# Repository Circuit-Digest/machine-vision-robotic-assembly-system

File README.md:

<div align="center">

# 🤖 Machine Vision-Based Robotic Assembly System Using MechArm 270 and Jetson Nano

**A real-time computer-vision system that drives a 6-DOF robotic arm + linear rail to autonomously assemble two toy cars, verifying every part placement using black-pixel ROI detection on an on-board webcam.**

<br><br>

</div>

---

## 📖 Table of Contents

1. [Project Overview](#-project-overview)
2. [Key Features](#-key-features)
3. [System Architecture](#-system-architecture)
4. [Hardware Requirements](#-hardware-requirements)
5. [Software Requirements & Installation](#-software-requirements--installation)
6. [Configuration](#-configuration)
7. [Running the Server](#-running-the-server)
8. [Dashboard Guide](#-dashboard-guide)
9. [Calibration Workflow](#-calibration-workflow)
10. [Vision Pipeline](#-vision-pipeline)
11. [Inspection Stations](#-inspection-stations)
12. [Waypoint System](#-waypoint-system)
13. [Socket.IO Event Reference](#-socketio-event-reference)
14. [Project Structure](#-project-structure)
15. [Troubleshooting](#-troubleshooting)
16. [Contributing](#-contributing)
17. [License](#-license)

---

## 🎯 Project Overview

This system orchestrates a **MechArm 270** 6-DOF robotic arm mounted on a **stepper-driven linear rail** to perform automated, vision-verified pick-and-place assembly of two toy cars.

The arm visits five physical stations. At each inspection station it positions its **wrist-mounted webcam** over a part tray, and a real-time OpenCV pipeline **verifies the correct component is present** using black-pixel ROI analysis before the arm is allowed to pick it up. A missing part immediately halts the sequence, triggers a **physical buzzer alert**, and waits for an operator to place the correct component.

The entire stack — robot control, vision processing, rail control, and web dashboards — runs as a **single Python process on port 5000**, eliminating all inter-service network latency.

---

## ✨ Key Features

| Feature | Description |
|---|---|
| 🎥 **Live MJPEG Stream** | Real-time webcam feed with annotated ROI overlays served to the browser |
| 🔍 **Black-Pixel ROI Detection** | Station-aware part detection using calibrated bounding boxes and HSV black masking |
| 🤖 **Wi-Fi Arm Control** | Non-blocking TCP socket control of MechArm 270 via `pymycobot` |
| 🚂 **ESP32 Rail Control** | HTTP-driven stepper linear rail with 5 presets (P1–P5) |
| 🚦 **Physical Indicators** | Green/Red LED + buzzer relay control for workshop-audible alerts |
| ✅ **Assembly Checklist** | Live progress bar and per-part checklist updating on every verification |
| 🖥️ **Three Dashboards** | Home display, Operator dashboard, Waypoint editor — all browser-based |
| 🛡️ **Sim Mode Fallback** | Full simulation when no hardware is connected — no code changes needed |
| 💾 **JSON Persistence** | All waypoints, poses, ROIs, and network config survive server restarts |

---

## 🏗️ System Architecture

```
┌─────────────────────────────────────────────────────────────────┐
│            main.py  (single process, port 5000)       │
│                                                                  │
│  ┌──────────────┐   ┌──────────────┐   ┌─────────────────────┐ │
│  │ RobotManager │   │  RailManager │   │  RailIndicatorMgr   │ │
│  │  Wi-Fi TCP   │   │  HTTP / ESP32│   │  HTTP relay control  │ │
│  └──────┬───────┘   └──────┬───────┘   └──────────┬──────────┘ │
│         │                  │                        │            │
│  ┌──────▼──────────────────▼───────────────────────▼──────────┐ │
│  │                   PlaybackEngine                            │ │
│  │  Sequences arm + rail movements + vision verification       │ │
│  └──────────────────────────┬──────────────────────────────────┘ │
│                             │  shared in-process memory           │
│  ┌──────────────────────────▼──────────────────────────────────┐ │
│  │             vision_thread()  (~30 FPS)                      │ │
│  │   OpenCV: Black-pixel ROI detection per station             │ │
│  └─────────────────────────────────────────────────────────────┘ │
│                                                                  │
│  Flask Routes + Socket.IO  →  Browser Dashboards                │
└─────────────────────────────────────────────────────────────────┘
```

### Data Flow

```
Camera → vision_thread → stable_detected_parts (dict)
                              ↓ (zero-latency in-process read)
                         PlaybackEngine → verifies part → continues sequence
                              ↓
                         Socket.IO → Browser (checklist, log, progress)
```

---

## 🔧 Hardware Requirements

| Component | Specification | Notes |
|---|---|---|
| **Robot Arm** | Elephant Robotics MechArm 270 | Wi-Fi model required |
| **Linear Rail** | Custom stepper rail with ESP32-C6 | 5 presets: P1–P5 |
| **Camera** | USB webcam (640×480 minimum) | Wrist-mounted on arm |
| **Relay Board** | 3-channel relay (12V) | Buzzer + Green/Red LED |
| **Network** | Wi-Fi AP or router | Arm, ESP32, and host PC on same LAN |
| **Host Computer** | Any x86/ARM Linux or Windows PC | Python 3.9+ required |

> [!NOTE]
> The system runs in full **simulation mode** if no hardware is connected. The camera stream is replaced by an animated mock feed, all Socket.IO events fire normally, and you can test the complete UI and checklist flow without any physical hardware.

---

## 💻 Software Requirements & Installation

### 1. Clone the repository

```bash
git clone https://github.com/YOUR_USERNAME/machine-vision-robotic-assembly-system.git
cd machine-vision-robotic-assembly-system
```

### 2. Create a virtual environment (recommended)

```bash
python -m venv venv

# Windows
venv\Scripts\activate

# Linux / macOS
source venv/bin/activate
```

### 3. Install dependencies

```bash
pip install -r requirements.txt
```

### Dependency Overview

| Package | Purpose |
|---|---|
| `flask` | Web server & template rendering |
| `flask-socketio` | Real-time WebSocket transport |
| `requests` | HTTP calls to the ESP32 Rail API |
| `pymycobot` | MechArm 270 Wi-Fi TCP SDK |
| `opencv-python` | Video capture, black-pixel ROI masking, MJPEG stream |
| `numpy` | Array operations for vision pipeline |

---

## ⚙️ Configuration

### Step 1 — Set your network IPs

Edit **`config.py`** and update the two IP constants at the bottom of the file:

```python
ARM_IP         = "192.168.1.100"   # Your MechArm270's Wi-Fi IP address
RAIL_IP        = "192.168.1.101"   # Your ESP32-C6 Rail controller IP
```

> [!TIP]
> You can also set these at runtime **without restarting the server** — open the Operator Dashboard, click the gear icon ⚙️, and enter your IPs. They are saved to `robot_config.json` and `rail_config.json` and take effect immediately.

### Step 2 — Camera index

In `config.py`, set the correct USB camera index:

```python
CAMERA_INDEX = 0    # 0 = default (first USB camera)
                    # 1 = second USB camera, etc.
```

### Step 3 — Vision detection thresholds

Tune these in `config.py` to match your lighting and part colours:

```python
# Black part detection
BLACK_HSV_LOWER = (0,   0,   0)    # HSV lower bound for black
BLACK_HSV_UPPER = (180, 255, 50)   # V < 50 = genuinely dark/black
BLACK_PIXEL_RATIO = 0.10           # 10% of ROI must be black to count as "present"

# Temporal hysteresis (noise suppression)
CONFIRM_FRAMES   = 5    # frames a part must be seen before "stable"
DISAPPEAR_FRAMES = 10   # frames a part must be missing before "lost"
```

### Step 4 — Runtime-persisted configuration files

The following JSON files are auto-generated and updated by the dashboards. They override the `config.py` defaults:

| File | Contents | Editable via |
|---|---|---|
| `robot_config.json` | Arm IP, port, axis calibration offsets | Operator Dashboard ⚙️ |
| `rail_config.json` | Rail ESP32 IP | Operator Dashboard ⚙️ |
| `camera_settings.json` | Brightness, contrast, exposure, gain | Operator Dashboard 🎥 |
| `scan_poses.json` | 6-joint arm angles per inspection station | Waypoint Editor → Scan Poses |
| `roi_boundaries.json` | Per-part pixel bounding boxes (ROI) | Operator Dashboard → ROI Editor |
| `zone_boundaries.json` | Spatial zone definitions per station | Operator Dashboard → Zone Editor |
| `waypoints.json` | Full arm + rail motion sequence | Waypoint Editor |

> [!WARNING]
> The `waypoints.json` included in this repository was recorded on a **specific physical rig**. Joint angles and positions will **not transfer** to a different robot or table layout. You must re-record all waypoints using the Waypoint Editor for your own setup.

---

## 🚀 Running the Server

```bash
python main.py
```

The server starts on `http://0.0.0.0:5000`. Open a browser and navigate to:

| URL | Dashboard |
|---|---|
| `http://localhost:5000/` | 🏠 Home Display Dashboard |
| `http://localhost:5000/camera_view` | 🖥️ Operator Dashboard |
| `http://localhost:5000/editor` | ✏️ Waypoint Editor |

On startup you will see:

```
======================================================================
  Robotic Assembly System (MechArm 270 & Jetson Nano) -> http://localhost:5000
  Robotic Arm + Stepper Linear Rail + Black-pixel ROI Vision Integrated.
======================================================================
```

The robot arm and rail connections are made in the background — if they fail the server continues in simulation mode and retries every 15 seconds.

---

## 🖥️ Dashboard Guide

### 🏠 Home Display Dashboard (`/`)

Clean status overview, suitable for display on a monitor during operation.

```
┌──────────────────────────┬──────────────────────┐
│   Live Camera Stream     │   System Info         │
│   (annotated MJPEG)      │   Robot: MechArm 270  │
│                          │   Detection: Black ROI│
├──────────────────────────┼──────────────────────┤
│   Last Detection         │  Assembly Progress   │
│   Snapshot               │  ████████░░░  75%    │
│                          │                      │
│                          │  ✅ Chassis 1         │
│                          │  ✅ Chassis 2         │
│                          │  ✅ WheelBase 1a      │
│                          │  ⏳ WheelBase 2a      │
│                          │  ...                  │
│                          │                      │
│                          │  Sensor: 24.3°C      │
│                          │  Door: CLOSED        │
│                          │                      │
│                          │  System Log          │
│                          │  ✓ Chassis 1 confirmed│
└──────────────────────────┴──────────────────────┘
```

- **▶ Play Sequence** — starts the full automated assembly run
- **⏹ Stop Arm** — emergency halt

### 🖥️ Operator Dashboard (`/camera_view`)

Full-featured operator view for monitoring and controlling the assembly:

- **Live annotated stream** — ROI boxes (grey → yellow → green), part labels, pixel-ratio readout, station overlay
- **Robot telemetry** — 6 joint angles, XYZ coordinates updated every 200 ms
- **Assembly checklist** — all parts for both cars, updating in real time
- **8-Switch Simulator Panel** — toggle any part as "present" for dry-run testing without physical components
- **Halt/Error Panel** — if the sequence stops on a missing part, this panel shows the reason and a restart button

### ✏️ Waypoint Editor (`/editor`)

Engineering tool for teaching the robot its motion sequence:

1. **Jog controls** — move each of the 6 joints or X/Y/Z coordinates from the browser
2. **Record** — save the current arm pose as a new waypoint (angles, coords, or both)
3. **Edit sequence** — rename, reorder, adjust speed, vacuum action, delay, and rail preset per waypoint
4. **Scan Pose console** — jog the arm to the perfect camera inspection angle, then click **Set P1** (or P2/P4/P5) to save to `scan_poses.json`
5. **Motor calibration** — lock/unlock individual joints, adjust motor power levels
6. **Network settings** — change Arm IP, Rail IP, and speed without restarting the server

---

## 📐 Calibration Workflow

Follow this sequence when setting up on a new physical rig:

```
1. Physical setup
   └─ Mount arm on rail, position part trays at stations P1, P2, P4, P5

2. Network configuration
   └─ Set ARM_IP and RAIL_IP in config.py or via Operator Dashboard ⚙️

3. Camera verification
   └─ Open /camera_view, check live stream
   └─ Adjust CAMERA_INDEX in config.py if wrong camera opens

4. Scan pose recording  (Waypoint Editor → 📸 Inspection Scan Poses)
   └─ Jog arm to view P1 tray → click "Set P1 (Chassis)"
   └─ Repeat for P2, P4, P5

5. ROI calibration  (Operator Dashboard → ROI Editor)
   └─ Move arm to scan pose for each station
   └─ Draw bounding boxes around each part slot on the video frame
   └─ Save → updates roi_boundaries.json

6. Detection threshold tuning  (config.py)
   └─ Adjust BLACK_PIXEL_RATIO until parts detect cleanly
   └─ Use 8-Switch Simulator to verify checklist behaviour

7. Waypoint recording  (Waypoint Editor)
   └─ Record pick positions at each station
   └─ Record place positions at P3 (assembly zone)
   └─ Add vision_check waypoints before each pick
   └─ Test with "Skip Vision" mode first, then enable vision checks

8. Full test run
   └─ Place parts at all stations
   └─ Click ▶ Play Sequence on Home Dashboard
   └─ Verify checklist completes 100%
```

---

## 👁️ Vision Pipeline

The vision system runs in a **dedicated background thread** at ~30 FPS using OpenCV.

### Black-Pixel ROI Detection

The only detection method used is black-pixel ratio analysis within calibrated Region of Interest (ROI) bounding boxes:

```
Frame (BGR)
  │
  ├─ GaussianBlur (5×5) → HSV conversion
  │
  └─ For each active part at current station:
        Crop frame to ROI bounding box  (from roi_boundaries.json)
        Apply black HSV mask: H[0-180] S[0-255] V[0-50]
        ratio = countNonZero(mask) / roi_area
        present = ratio - ambient_baseline ≥ BLACK_PIXEL_RATIO (10%)
```

An **adaptive ambient baseline** is captured on the first frame after the arm settles at its scan pose. This compensates automatically for dim environments or dark surfaces in the background.

### How Detection Works Per Station

1. Rail moves arm to station (e.g. P1)
2. Arm commands itself to pre-saved scan pose for that station (`scan_poses.json`)
3. Vision thread activates and begins checking only the parts registered to that station (`STATION_PARTS` in `config.py`)
4. For each active part slot, it crops the frame to the ROI (`roi_boundaries.json`) and measures the black-pixel ratio
5. Parts meeting the threshold are accumulated over frames; confirmed after `CONFIRM_FRAMES` consecutive detections

### Hysteresis Filtering

Raw frame results are not immediately acted upon — a two-stage filter prevents false positives from motion blur, shadows, or lighting glitches:

```
MISSING ──[seen for 5 consecutive frames]──→ STABLE (detected)
STABLE  ──[missing for 10 consecutive frames]──→ MISSING
```

### Stream Annotation

During an active vision check, the live stream shows:

- **Grey boxes** — ROI is active, part not detected
- **Yellow boxes** — part seen but not yet stable (accumulating frames)
- **Green boxes** — part confirmed stable (checkmark ✓ + ratio %)
- **Station panel** — current station label + list of active part slots

---

## 🏭 Inspection Stations

| Station | Preset | Detection Method | Parts Verified |
|---|---|---|---|
| **P1** | `P1 (Chassis)` | Black-pixel ROI | Chassis 1, Chassis 2 |
| **P2** | `P2 (Wheelbase)` | Black-pixel ROI | WheelBase 1a, 2a, 1b, 2b |
| **P3** | `P3 (Assemble)` | *(none — assembly zone)* | — |
| **P4** | `P4 (Wheels)` | Black-pixel ROI (8 slots) | Wheel Slots 1–8 |
| **P5** | `P5 (Body)` | Black-pixel ROI | Body 1, Body 2 |

---

## 📋 Waypoint System

### Waypoint Record Format

```json
{
  "name": "Pick Chassis 1",
  "type": "angles",
  "data": [15.2, -45.1, 90.0, 0.0, 45.0, 0.0],
  "speed": 40,
  "vacuum": "on",
  "vacuum_delay_ms": 300,
  "delay_ms": 200,
  "rail_preset": "P1"
}
```

| Field | Values | Description |
|---|---|---|
| `type` | `angles`, `coords`, `both`, `vision_check` | Movement type |
| `data` | `[j1, j2, j3, j4, j5, j6]` or `[x, y, z, rx, ry, rz]` | Target position |
| `vacuum` | `"on"`, `"off"`, `"none"` | Vacuum pump action after movement |
| `rail_preset` | `"P1"`–`"P5"`, `"NONE"` | Rail position to move to after arm arrives |
| `speed` | `1`–`100` | Arm movement speed percentage |

### `vision_check` Waypoint

A special waypoint type that **does not move the arm or rail**. It triggers a vision verification cycle:

```json
{
  "name": "Verify Chassis 1",
  "type": "vision_check",
  "rail_preset": "P1",
  "check_part": "Chassis 1"
}
```

When the PlaybackEngine reaches this waypoint it:
1. Commands the arm to the pre-saved scan pose for that station
2. Waits 1.5 s for mechanical settling
3. Activates vision detection for the named part
4. Waits until the part is stably detected (or halts on timeout/stop)
5. Emits `part_verified` to update the UI checklist

---

## 📡 Socket.IO Event Reference

### Server → Client

| Event | Key Payload Fields | Description |
|---|---|---|
| `robot_status` | `angles[]`, `coords[]`, `rail{}`, `vision_detected[]` | Full telemetry broadcast (every 200 ms) |
| `status` | `state`, `step`, `total`, `message` | Playback state machine update |
| `playback_progress` | `index`, `total`, `name`, `state` | Per-waypoint progress update |
| `part_verified` | `part`, `rail`, `snapshot_ts` | Part confirmed — update checklist |
| `vision_log` | `level`, `message` | Colour-coded log line for consoles |
| `detection_started` | `part`, `station` | Vision scan is active |
| `detection_stopped` | `part`, `station`, `found` | Vision scan ended |
| `snapshot_updated` | *(none)* | Last-detection image on disk has changed |
| `error` | `part`, `position`, `message` | Emergency stop / verification fault |
| `command_complete` | `action`, `cmd_id` | Arm command acknowledged by hardware |

### Client → Server

| Event | Payload | Description |
|---|---|---|
| `play_sequence` | `start_index`, `speed`, `skip_vision` | Start playback |
| `stop_sequence` | *(none)* | Emergency stop |
| `toggle_mock` | `part`, `value` | Toggle hardware simulator switch |
| `jog_joint` | `joint`, `delta`, `speed` | Move one joint by delta degrees |
| `jog_coord` | `axis`, `delta`, `speed` | Move in Cartesian space |
| `record_waypoint` | `type`, `name`, `vacuum`, `rail_preset`, `speed` | Save current pose |
| `set_scan_pose` | `station` | Save current arm angles as scan pose |
| `update_ip` | `arm_ip`, `rail_ip` | Change network config without restart |

---

## 📁 Project Structure

```
machine-vision-robotic-assembly-system/
│
├── main.py                    # Main Flask + SocketIO application (2,700+ lines)
├── config.py                  # Shared constants: IPs, HSV thresholds, station maps
├── requirements.txt           # Python dependencies
├── .gitignore                 # Excludes __pycache__, logs, runtime snapshots
├── LICENSE                    # MIT License
│
├── templates/
│   ├── home.html              # 🏠 Home display (live feed + status checklist)
│   ├── operator_view.html     # 🖥️  Operator Dashboard (full telemetry + controls)
│   └── waypoint_editor.html   # ✏️  Waypoint Editor & Scan Pose console
│
├── static/
│   └── socket.io.min.js       # Socket.IO client (served locally, no CDN dependency)
│
├── hardware/                  # 🔌 PCB & Schematic Design Files
│   ├── schematic.pdf          # PCB schematic diagram (PDF)
│   ├── gerbers.zip            # Manufacturing-ready Gerber files
│   ├── controller.kicad_sch   # KiCad Schematic design
│   ├── controller.kicad_pcb   # KiCad PCB board layout
│   ├── controller.kicad_pro   # KiCad Project file
│   └── controller.kicad_prl   # KiCad Project local settings
│
├── Images/                    # 🖼️ Documentation Media Files
│   ├── vision_demo.gif        # Animated GIF showing the real-time vision tracking
│   ├── pcb_render.png         # 3D render of the custom PCB board
│   ├── pcb_layout.png         # 2D layout layout of the PCB routing
│   ├── control_panel.jpg      # Physical photo/render of the control panel
│   └── cad_render.png         # 3D CAD rendering of the full assembly layout
│
├── waypoints.json             # Recorded motion sequence (re-record for your rig)
├── scan_poses.json            # Camera inspection arm poses per station
├── roi_boundaries.json        # Calibrated per-part ROI bounding boxes (pixels)
├── zone_boundaries.json       # Spatial zone definitions per station
├── camera_settings.json       # USB camera brightness/contrast/exposure settings
├── robot_config.json          # Runtime arm IP config (overrides config.py)
└── rail_config.json           # Runtime rail IP config (overrides config.py)
```

---

## 🔧 Troubleshooting

### Robot arm won't connect

- Confirm the MechArm 270 is powered on and joined to your Wi-Fi network
- Check `ARM_IP` in `config.py` or `robot_config.json` matches the arm's actual IP
- The arm's IP is shown on the robot's display or in your router's DHCP table
- The server retries the connection every 15 seconds — check the console for `Wi-Fi connect failed` messages

### Rail won't move

- Confirm the ESP32-C6 board is powered and on the same LAN
- Check `RAIL_IP` in `config.py` or `rail_config.json`
- Open `http://YOUR_RAIL_IP/status` in a browser — you should get a JSON response

### Camera not opening / black screen

- Try changing `CAMERA_INDEX` in `config.py` (0, 1, 2 …)
- On Linux, if using V4L2: ensure `CAMERA_BACKEND = "CAP_V4L2"` in `config.py`
- Check that no other application has the camera locked

### Parts not being detected

- Verify the arm reaches the correct scan pose (check `scan_poses.json`)
- Use the **ROI Editor** in the Operator Dashboard to confirm the bounding boxes are positioned over the part slots
- Lower `BLACK_PIXEL_RATIO` in `config.py` if detection is too strict
- Check ambient lighting — very bright or uneven light can wash out the black pixel mask

### Detection works in sim but not on hardware

- Verify `roi_boundaries.json` is calibrated for your actual camera view angle (sim uses default zones)
- Re-run the scan pose recording for each station in the Waypoint Editor

---

## 🤝 Contributing

Contributions, bug reports, and feature suggestions are welcome!

1. **Fork** the repository
2. Create a feature branch: `git checkout -b feature/your-feature-name`
3. Commit your changes: `git commit -m "feat: add your feature description"`
4. Push to your fork: `git push origin feature/your-feature-name`
5. Open a **Pull Request** against the `main` branch

### Code Style

- Python: follow [PEP 8](https://pep8.org/)
- Docstrings: include for all new public functions and classes
- Existing `# ─────` section dividers should be preserved for consistency

---

## 📄 License

This project is licensed under the **MIT License** — see the [LICENSE](LICENSE) file for details.

---

<div align="center">

Built with ❤️ using **Flask · OpenCV · pymycobot · Socket.IO**

</div>

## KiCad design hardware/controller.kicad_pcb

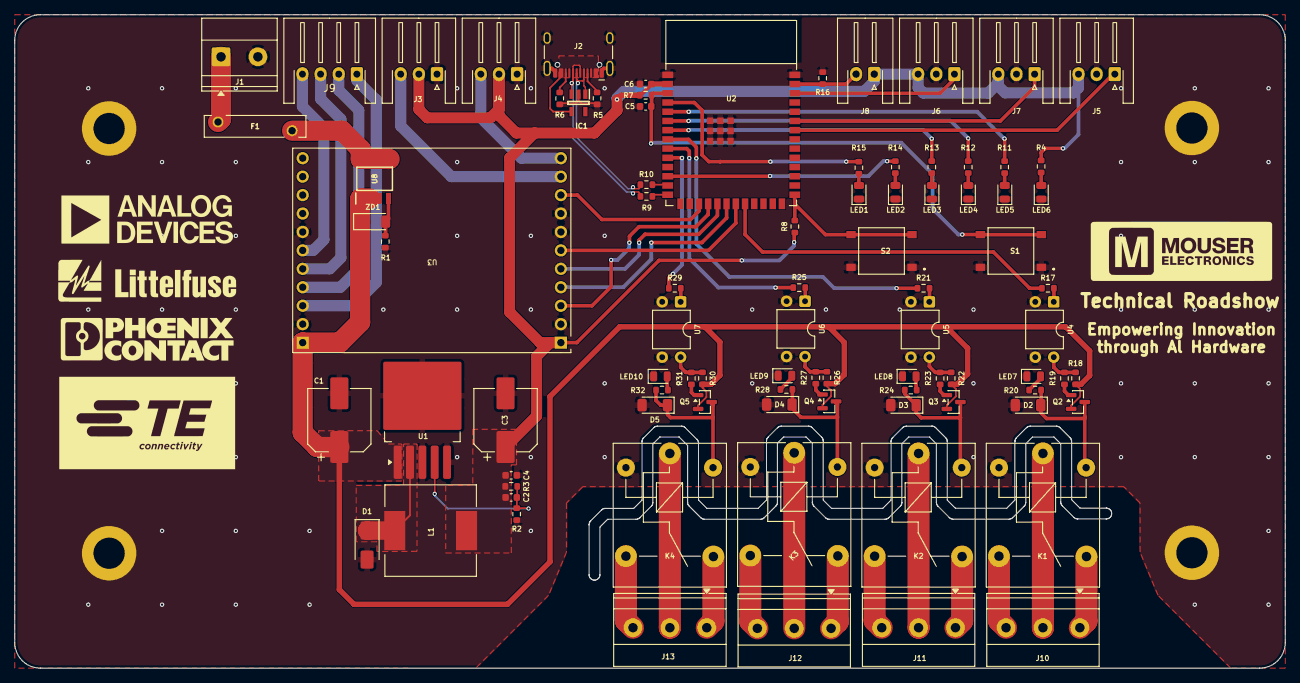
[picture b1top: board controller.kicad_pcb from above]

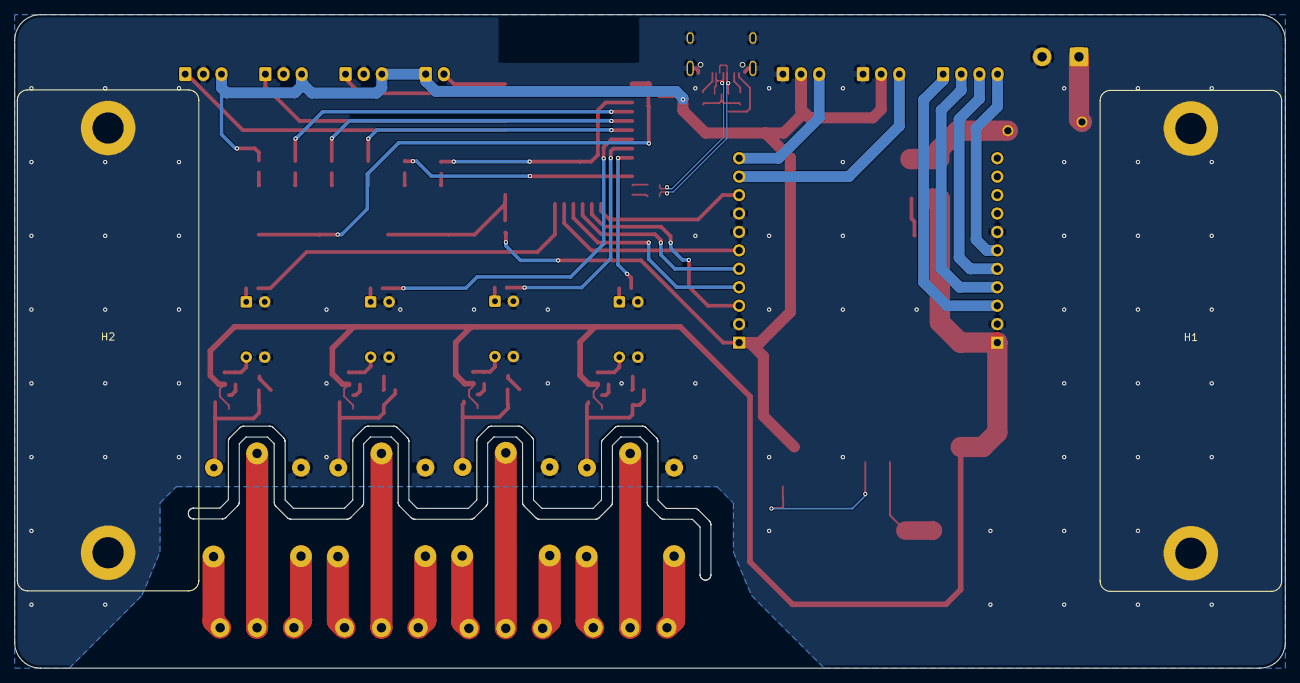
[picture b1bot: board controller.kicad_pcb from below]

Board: 2 copper layers, 175.0 x 90.0 mm, 90 parts (2 on the bottom side), 79 nets.

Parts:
C1, C3: 220uF; CP_Elec_8x10.5
C2: 3.3nF; C_0603_1608Metric
C4: 0.22uF; C_0603_1608Metric
C5, C6: 0.1uF; C_0603_1608Metric
D1: SS34; D_SMA
D2, D3, D4, D5: LL4148; D_MiniMELF
F1: Polyfuse; 30R500UF
H1, H2: MountingHole_Pad; DinRailMount
IC1: SP0504BAHTG; SOT95P280X145-5N
J1: Screw_Terminal_01x02; TerminalBlock_Phoenix_MKDS-1,5-2-5.08_1x02_P5.08mm_Horizont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
J2: USB_C_Receptacle_USB2.0; USB_C_Receptacle_HCTL_HC-TYPE-C-16P-01A
J3, J4, J5, J6, J7: Conn_01x03; JST_XH_S3B-XH-A-1_1x03_P2.50mm_Horizontal
J8: Conn_01x02; JST_XH_S2B-XH-A-1_1x02_P2.50mm_Horizontal
J9: Conn_01x04; JST_XH_S4B-XH-A-1_1x04_P2.50mm_Horizontal
J10, J11, J12, J13: Screw_Terminal_01x03; TerminalBlock_Phoenix_MKDS-1,5-3-5.08_1x03_P5.08mm_Horizont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
K1, K2, K3, K4: SANYOU_SRD_Form_C; Relay_SPDT_SANYOU_SRD_Series_Form_C
L1: 47uH; L_12x12mm_H8mm
LED1, LED2, LED3, LED4, LED5: LED Red; LED_0805_2012Metric
LED6, LED7, LED8, LED9, LED10: 3mm Red LED with 13mm Spacer; LED_0805_2012Metric
Q2, Q3, Q4, Q5: SS8550; SOT-23
R1: 100K; R_0603_1608Metric
R2, R4, R11, R12, R13, R14, R15, R17, R19, R20, R21, R23, R24, R25, R27, R28, R29, R31, R32: 1K; R_0603_1608Metric
R3: 0R; R_0603_1608Metric
R5, R6: 5K1; R_0603_1608Metric
R7, R8, R16, R18, R22, R26, R30: 10K; R_0603_1608Metric
R9, R10: 33R; R_0603_1608Metric
S1, S2: PTS641_SM25_SMTR2_LFS; PTS641SM25SMTR2LFS
U1: LM2596S-3.3; TO-263-5_TabPin3
U2: ESP32-S3-WROOM-1
U3: TMC5160_BOB
U4, U5, U6, U7: PC817; DIP-4_W7.62mm
U8: SI4463CDY-T1-GE3; SOIC127P600X175-8N
ZD1: 10V; D_MiniMELF

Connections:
+3.3V: C2.2, C3.1, C4.1, C6.1, J3.2, J4.2, J5.3, J6.3, J7.3, J8.1, L1.2, R3.1, R4.1, R7.1, R8.1, U2.2 (3V3), U3.1 (VCC_IO)
+12V: F1.1, J1.1
/EN: C5.1, R7.2, S1.3 (NO_1), S1.4 (NO_2), U2.3 (EN)
/IO0: R8.2, S2.3 (NO_1), S2.4 (NO_2), U2.27 (GPIO0/BOOT)
/IO1: J8.2, R16.2, U2.39 (GPIO1/TOUCH1/ADC1_CH0)
/IO2: J6.1, U2.38 (GPIO2/TOUCH2/ADC1_CH1)
/IO4: R15.1, U2.4 (GPIO4/TOUCH4/ADC1_CH3)
/IO5: R11.1, U2.5 (GPIO5/TOUCH5/ADC1_CH4)
/IO6: R12.1, U2.6 (GPIO6/TOUCH6/ADC1_CH5)
/IO7: R13.1, U2.7 (GPIO7/TOUCH7/ADC1_CH6)
/IO8: R14.1, U2.12 (GPIO8/TOUCH8/ADC1_CH7/SUBSPICS1)
/IO9: U2.17 (GPIO9/TOUCH9/ADC1_CH8/FSPIHD/SUBSPIHD), U3.9 (DRV_ENN)
/IO10: U2.18 (GPIO10/TOUCH10/ADC1_CH9/FSPICS0/FSPIIO4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), U3.3 (CSN)
/IO11: U2.19 (GPIO11/TOUCH11/ADC2_CH0/FSPID/FSPIIO5/S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), U3.5 (SDI)
/IO12: U2.20 (GPIO12/TOUCH12/ADC2_CH1/FSPICLK/FSPIIO6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), U3.4 (SCK)
/IO13: U2.21 (GPIO13/TOUCH13/ADC2_CH2/FSPIQ/FSPIIO7/S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), U3.6 (SDO)
/IO14: R17.1, U2.22 (GPIO14/TOUCH14/ADC2_CH3/FSPIWP/FSPIDQS/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)
/IO15: R21.1, U2.8 (GPIO15/U0RTS/ADC2_CH4/XTAL_32K_P)
/IO16: R25.1, U2.9 (GPIO16/U0CTS/ADC2_CH5/XTAL_32K_NH5)
/IO17: R29.1, U2.10 (GPIO17/U1TXD/ADC2_CH6)
/IO41: J5.1, U2.34 (MTDI/GPIO41/CLK_OUT1)
/IO42: J7.1, U2.35 (MTMS/GPIO42)
/REFL: J3.3, U3.10 (REFL)
/REFR: J4.3, U3.11 (REFR)
/USB_D+: IC1.3 (K_2), J2.A6 (D+), J2.B6 (D+), R9.1
/USB_D-: IC1.1 (K_1), J2.A7 (D-), J2.B7 (D-), R10.1
GND: C1.2, C3.2, C4.2, C5.2, C6.2, D1.2 (A), D2.2 (A), D3.2 (A), D4.2 (A), D5.2 (A), H1.1 (1_1), H2.1 (1_1), IC1.2 (A/K), J1.2, J2.A1 (GND), J2.A12 (GND), J2.B1 (GND), J2.B12 (GND), J2.SH (SHIELD), J3.1, J4.1, J5.2, J6.2, J7.2, K1.2, K2.2, K3.2, K4.2, LED1.1 (K), LED2.1 (K), LED3.1 (K), LED4.1 (K), LED5.1 (K), LED6.1 (K), LED7.1 (K), LED8.1 (K), LED9.1 (K), LED10.1 (K), R1.2, R2.2, R5.1, R6.1, R16.1, S1.1 (COM_1), S1.2 (COM_2), S2.1 (COM_1), S2.2 (COM_2), U1.3 (GND), U1.5 (~ON/OFF), U2.1 (GND), U2.40 (GND), U2.41 (GND), U3.2 (GND), U3.7 (GND), U3.8 (CLK16), U3.16 (GND), U3.21 (GND), U4.2, U4.3, U5.2, U5.3, U6.2, U6.3, U7.2, U7.3
unnamed: D1.1 (K), L1.1, U1.2 (OUT)
unnamed: D2.1 (K), K1.5, Q2.3 (C), R20.2
unnamed: D3.1 (K), K2.5, Q3.3 (C), R24.2
unnamed: D4.1 (K), K3.5, Q4.3 (C), R28.2
unnamed: D5.1 (K), K4.5, Q5.3 (C), R32.2
unnamed: J2.A5 (CC1), R5.2
unnamed: J2.B5 (CC2), R6.2
unnamed: J9.1, U3.20 (B2)
unnamed: J9.2, U3.19 (B1)
unnamed: J9.3, U3.18 (A2)
unnamed: J9.4, U3.17 (A1)
unnamed: J10.1, K1.4
unnamed: J10.2, K1.1
unnamed: J10.3, K1.3
unnamed: J11.1, K2.4
unnamed: J11.2, K2.1
unnamed: J11.3, K2.3
unnamed: J12.1, K3.4
unnamed: J12.2, K3.1
unnamed: J12.3, K3.3
unnamed: J13.1, K4.4
unnamed: J13.2, K4.1
unnamed: J13.3, K4.3
unnamed: LED6.2 (A), R4.2
unnamed: LED5.2 (A), R11.2
unnamed: LED4.2 (A), R12.2
unnamed: LED3.2 (A), R13.2
unnamed: LED2.2 (A), R14.2
unnamed: LED1.2 (A), R15.2
unnamed: LED7.2 (A), R20.1
unnamed: LED8.2 (A), R24.1
unnamed: LED9.2 (A), R28.1
unnamed: LED10.2 (A), R32.1
unnamed: Q2.1 (B), R19.2
unnamed: Q3.1 (B), R23.2
unnamed: Q4.1 (B), R27.2
unnamed: Q5.1 (B), R31.2
unnamed: R17.2, U4.1
unnamed: R18.1, R19.1, U4.4
unnamed: R21.2, U5.1
unnamed: R22.1, R23.1, U5.4
unnamed: R25.2, U6.1
unnamed: R26.1, R27.1, U6.4
unnamed: R29.2, U7.1
unnamed: R30.1, R31.1, U7.4
unnamed: C2.1, R2.1, R3.2, U1.4 (FB)
unnamed: R10.2, U2.13 (GPIO19/U1RTS/ADC2_CH8/CLK_OUT2/USB_D-)
unnamed: R9.2, U2.14 (GPIO20/U1CTS/ADC2_CH9/CLK_OUT1/USB_D+)
unnamed: F1.2, U8.5 (D_1), U8.6 (D_2), U8.7 (D_3), U8.8 (D_4)
unnamed: R1.1, U8.4 (G), ZD1.2 (A)
VBUS: IC1.4 (K_3), J2.A4 (VBUS), J2.A9 (VBUS), J2.B4 (VBUS), J2.B9 (VBUS)
VDC: C1.1, Q2.2 (E), Q3.2 (E), Q4.2 (E), Q5.2 (E), R18.2, R22.2, R26.2, R30.2, U1.1 (VIN), U3.22 (VM), U8.1 (S_1), U8.2 (S_2), U8.3 (S_3), ZD1.1 (K)
